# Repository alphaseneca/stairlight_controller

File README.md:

# stairlight_controller

This GitHub repository houses the code and documentation for a Two-Way Passive Infrared (PIR) Stairlight Controller. The controller incorporates PIR sensors to detect motion in both ascending and descending directions, ensuring that the stairlights illuminate when needed and conserve energy when not in use.

## Schematic

The schematic for the device connection is shown below.

## Setting it up.

**Translating Schematic to PCB and Integrating Components:**
Following the meticulous design of the schematic, the next phase involves transposing this plan onto a printed circuit board (PCB). For rapid prototyping and flexibility, a prefboard serves as an excellent choice to bring the schematic to life. This stage allows for a physical manifestation of the electronic layout, facilitating quick adjustments and component placements as needed. Upon transferring the design, selecting an appropriate housing for the circuit becomes pivotal. The chosen housing not only provides protection but also accommodates the PCB and its components snugly. Additionally, this phase involves the crucial step of integrating Passive Infrared (PIR) sensors into the controller setup. These sensors, once connected, enable the controller to detect motion effectively and trigger the desired response in the staircase lighting system. Assembling the components within the selected housing, ensuring meticulous connections between the PCB, PIR sensors, and the controller, ensures a cohesive and functional unit.

---

---

## PIR Sensors

The PIR sensors are connected to the controller's input pins. These sensors are mounted on the poles of the stairs beforehand and are used to detect motion in both ascending and descending directions.

## Addressing False Triggers:

During the integration phase, an important realization surfaced regarding the initial setup. Due to the absence of pull-down resistors, certain values were floating, leading to sporadic false triggers within the system. To rectify this issue and ensure stable operation, 10k resistors were strategically added. These resistors served as pull-down components, stabilizing the values and preventing erratic triggering, thus enhancing the reliability and accuracy of the staircase light controller's functionality.

## More Images of the setup.

## Code

The code for the controller is available on GitHub.
[\stairlight_controller_code](https://github.com/alphaseneca/stairlight_controller/tree/master/stairlight_controller_code)

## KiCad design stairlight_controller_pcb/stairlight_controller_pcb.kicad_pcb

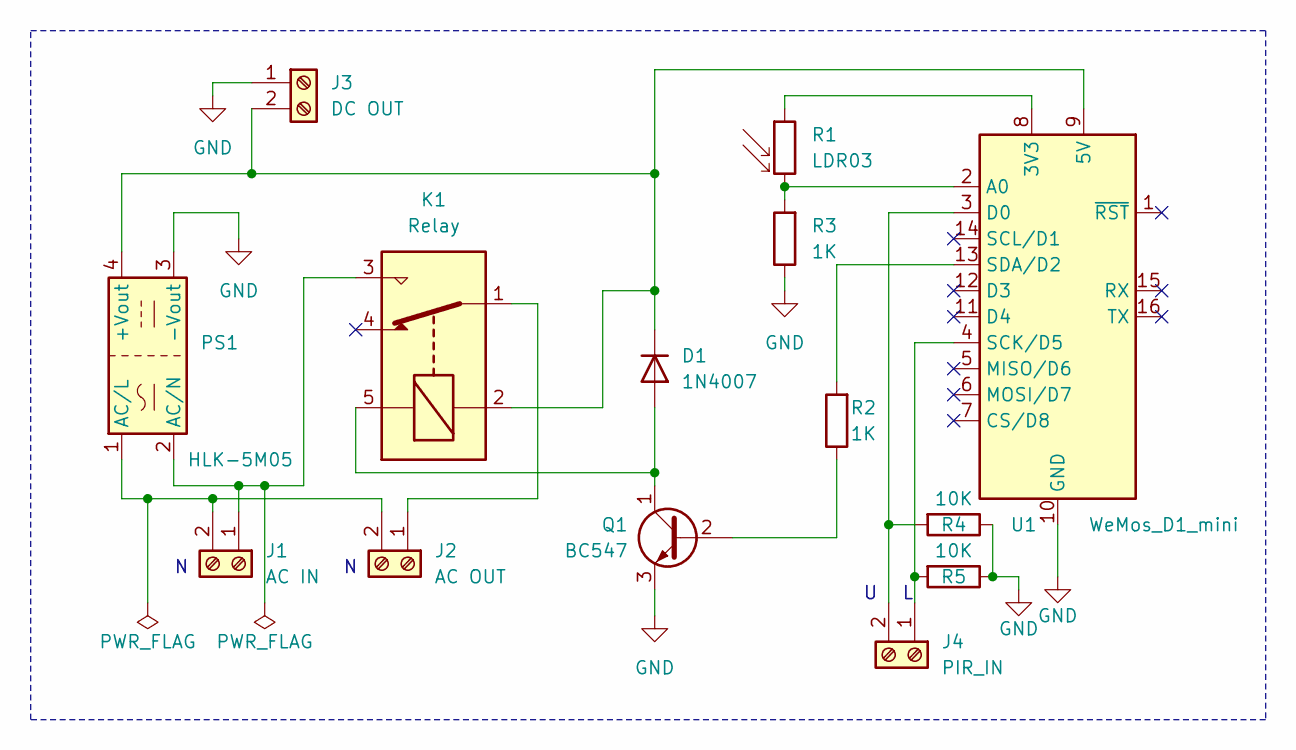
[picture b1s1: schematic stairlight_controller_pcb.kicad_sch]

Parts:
D1: 1N4007; D_DO-41_SOD81_P10.16mm_Horizontal
J1: AC IN; TerminalBlock_Altech_AK300-2_P5.00mm
J2: AC OUT; TerminalBlock_Altech_AK300-2_P5.00mm
J3: DC OUT; TerminalBlock_Altech_AK300-2_P5.00mm
J4: PIR_IN; TerminalBlock_Altech_AK300-2_P5.00mm
K1: Relay; Relay_SPDT_SANYOU_SRD_Series_Form_C
PS1: HLK-5M05; Converter_ACDC_HiLink_HLK-5Mxx
Q1: BC547; TO-92_Inline
R1: LDR03; R_LDR_5.0x4.1mm_P3mm_Vertical
R2, R3: 1K; R_Axial_DIN0204_L3.6mm_D1.6mm_P5.08mm_Horizontal
R4, R5: 10K; R_Axial_DIN0204_L3.6mm_D1.6mm_P5.08mm_Horizontal
U1: WeMos_D1_mini; WEMOS_D1_mini_light

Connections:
GND: J3.1, PS1.3 (-Vout), Q1.3 (E), R3.1, R4.1, R5.1, U1.10 (GND)
unnamed: D1.2 (A), K1.5, Q1.1 (C)
unnamed: D1.1 (K), J3.2, K1.2, PS1.4 (+Vout), U1.9 (5V)
unnamed: J1.1, K1.3, PS1.2 (AC/N)
unnamed: J1.2, J2.2, PS1.1 (AC/L)
unnamed: J2.1, K1.1
unnamed: J4.1, R5.2, U1.4 (SCK/D5)
unnamed: J4.2, R4.2, U1.3 (D0)
unnamed: Q1.2 (B), R2.1
unnamed: R1.1, U1.8 (3V3)
unnamed: R1.2, R3.2, U1.2 (A0)
unnamed: R2.2, U1.13 (SDA/D2)

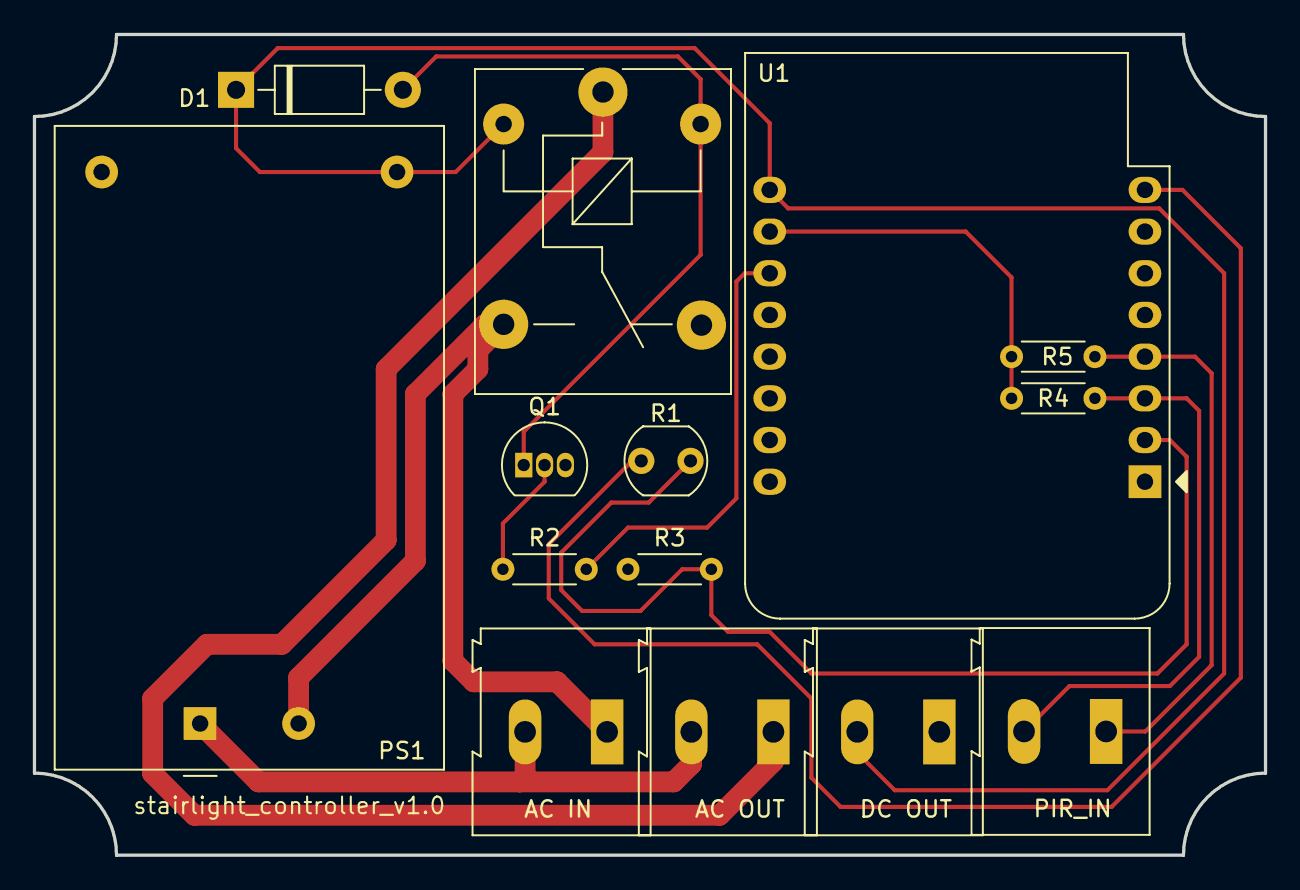
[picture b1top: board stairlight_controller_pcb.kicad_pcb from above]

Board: 2 copper layers, 75.0 x 50.0 mm, 14 parts (0 on the bottom side), 12 nets.

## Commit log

2023-11-06 Added README.md
2023-11-06 Added code
2023-11-06 Added pcb files
2023-11-06 Added schematic
2023-11-06 Added schematic on readme
2023-11-22 Uploaded the final code
2023-11-22 Added comments to the code
2023-11-22 Added all the images
2023-11-22 Final Schematic and PCB
2023-11-22 Fixed the broken link
